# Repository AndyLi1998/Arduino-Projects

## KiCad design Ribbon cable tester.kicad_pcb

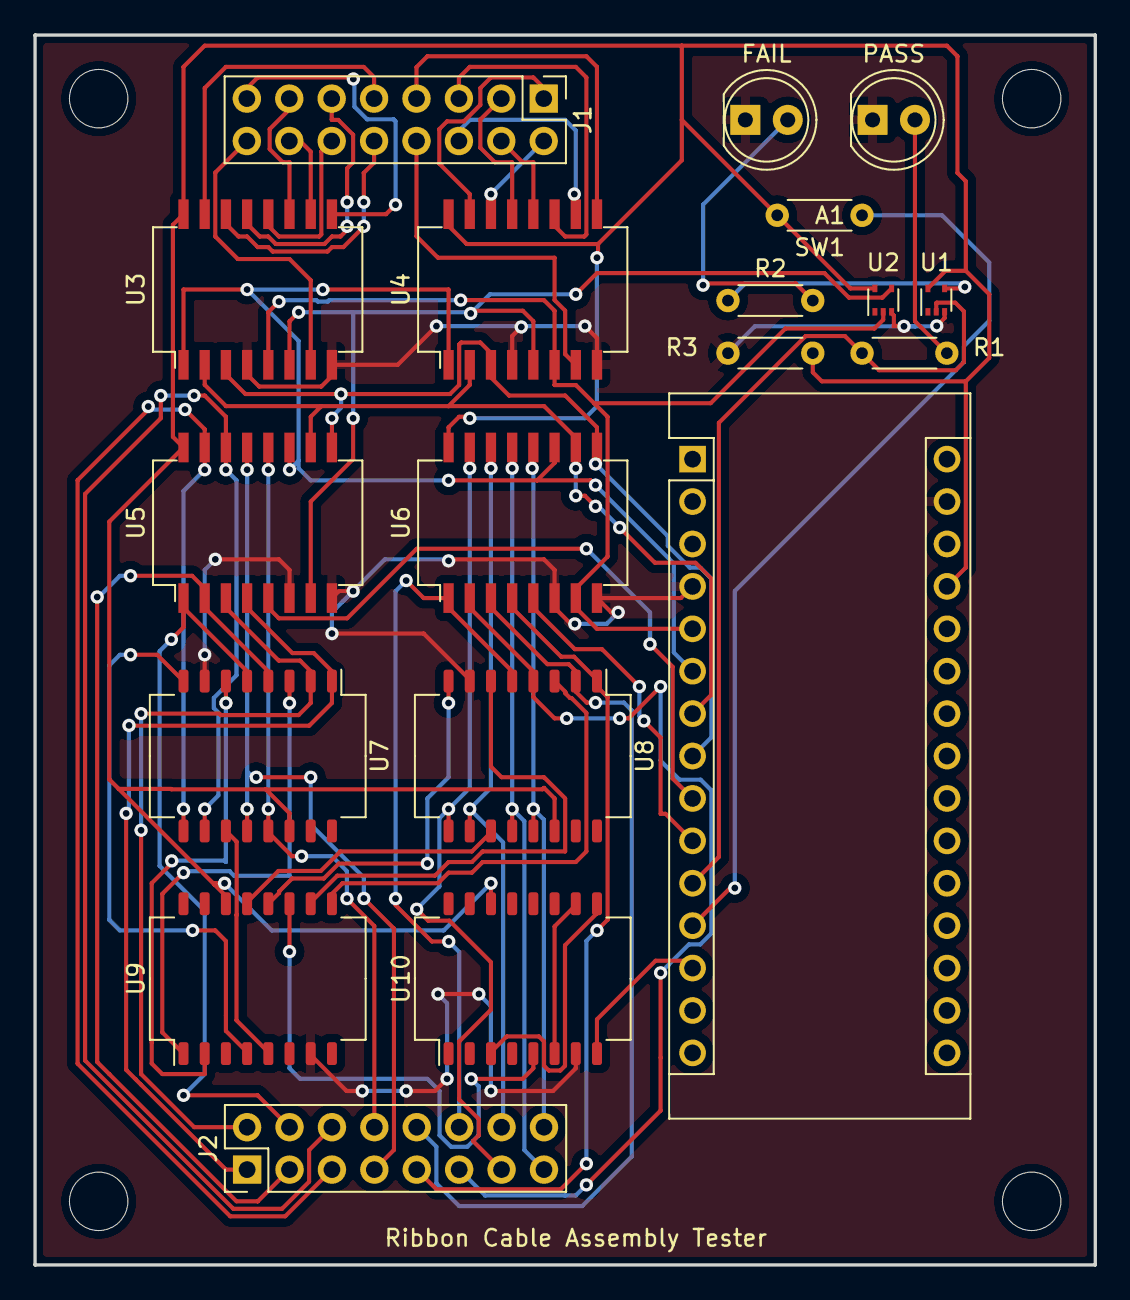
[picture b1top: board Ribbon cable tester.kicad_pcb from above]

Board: 2 copper layers, 63.5 x 73.7 mm, 19 parts (0 on the bottom side), 61 nets.

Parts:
A1: Arduino_Nano_v3.x; Arduino_Nano
FAIL: LED_Small_Filled; LED_D5.0mm
J1, J2: Conn_02x08_Counter_Clockwise; PinHeader_2x08_P2.54mm_Vertical
PASS: LED_Small_Filled; LED_D5.0mm
R1, R2, R3: R_Small_US; R_Axial_DIN0204_L3.6mm_D1.6mm_P5.08mm_Horizontal
SW1: SW_Push; R_Axial_DIN0204_L3.6mm_D1.6mm_P5.08mm_Horizontal
U1, U2: 74LVC1GU04DRL; SOT-553
U3, U4: 74HCT237; Transformer_Ethernet_Bel_S558-5999-T7-F
U5, U6: 74LS151; Transformer_Ethernet_Bel_S558-5999-T7-F
U7, U8, U9: 74LS86; Transformer_Ethernet_Halo_N2_SO-16_7.11x12.7mm
U10: 74HC86; Transformer_Ethernet_Halo_N2_SO-16_7.11x12.7mm

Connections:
/FirstRowPass: A1.9 (D6), U5.5 (Z)
/LED_Power: A1.11 (D8), R1.1, U1.2
/SecondRowPass: A1.10 (D7), U6.5 (Z)
/Sel0: A1.5 (D2), U2.2, U3.5 (~E1), U4.6 (E2), U6.7 (~E)
/Sel1: A1.6 (D3), U3.1 (A0), U4.1 (A0), U5.11 (S0), U6.11 (S0)
/Sel2: A1.7 (D4), U3.2 (A1), U4.2 (A1), U5.10 (S1), U6.10 (S1)
/Sel3: A1.8 (D5), U3.3 (A2), U4.3 (A2), U5.9 (S2), U6.9 (S2)
/Short_check: A1.13 (D10), U10.8
/Start_but: A1.12 (D9), SW1.1
/Vcc: A1.27 (+5V), R3.2, SW1.2, U1.5 (VCC), U2.5 (VCC), U3.16 (VCC), U4.16 (VCC), U5.16 (VCC), U6.16 (VCC), U7.14 (VCC), U8.14 (VCC), U9.14 (VCC), U10.14 (VCC)
/notSel0: U2.4, U3.6 (E2), U4.5 (~E1), U5.7 (~E)
/sig1: J2.1, U5.4 (I0), U7.1
/sig2: J2.2, U5.3 (I1), U7.2
/sig3: J2.3, U5.2 (I2), U7.4
/sig4: J2.4, U5.1 (I3), U7.5
/sig5: J2.5, U5.15 (I4), U7.9
/sig6: J2.6, U5.14 (I5), U7.10
/sig7: J2.7, U5.13 (I6), U7.12
/sig8: J2.8, U5.12 (I7), U7.13
/sig9: J2.9, U6.4 (I0), U8.1
/sig10: J2.10, U6.3 (I1), U8.2
/sig11: J2.11, U6.2 (I2), U8.4
/sig12: J2.12, U6.1 (I3), U8.5
/sig13: J2.13, U6.15 (I4), U8.9
/sig14: J2.14, U6.14 (I5), U8.10
/sig15: J2.15, U6.13 (I6), U8.12
/sig16: J2.16, U6.12 (I7), U8.13
GNDREF: A1.4 (GND), A1.29 (GND), FAIL.1 (K), PASS.1 (K), R3.1, U1.3 (GND), U2.3 (GND), U3.4 (~LE), U3.8 (GND), U4.4 (~LE), U4.8 (GND), U5.6 (~Z), U5.8 (GND), U6.6 (~Z), U6.8 (GND), U7.7 (GND), U8.7 (GND), U9.7 (GND), U10.7 (GND)
unnamed: PASS.2 (A), R1.2
unnamed: FAIL.2 (A), R2.2
unnamed: J1.1, U4.15 (Y0)
unnamed: J1.2, U4.14 (Y1)
unnamed: J1.3, U4.13 (Y2)
unnamed: J1.4, U4.12 (Y3)
unnamed: J1.5, U4.11 (Y4)
unnamed: J1.6, U4.10 (Y5)
unnamed: J1.7, U4.9 (Y6)
unnamed: J1.8, U4.7 (Y7)
unnamed: J1.9, U3.15 (Y0)
unnamed: J1.10, U3.14 (Y1)
unnamed: J1.11, U3.13 (Y2)
unnamed: J1.12, U3.12 (Y3)
unnamed: J1.13, U3.11 (Y4)
unnamed: J1.14, U3.10 (Y5)
unnamed: J1.15, U3.9 (Y6)
unnamed: J1.16, U3.7 (Y7)
unnamed: R2.1, U1.4
unnamed: U7.3, U9.1
unnamed: U7.6, U9.2
unnamed: U7.8, U9.4
unnamed: U7.11, U9.5
unnamed: U8.3, U9.9
unnamed: U8.6, U9.10
unnamed: U8.8, U9.12
unnamed: U8.11, U9.13
unnamed: U9.3, U10.1
unnamed: U9.6, U10.2
unnamed: U10.3, U10.9
unnamed: U9.8, U10.4
unnamed: U9.11, U10.5
unnamed: U10.6, U10.10

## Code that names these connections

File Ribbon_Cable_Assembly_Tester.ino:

int Sel0=2; 
int Sel1=3;
int Sel2=4;
int Sel3=5;
int FRP=6; //First Row Pass
int SRP=7; //Second Row Pass
int LED_Power=8; //one pin power two LED, default condition FAIL light on
int start_button=9;
int short_check=10;
int counter=0;


void setup() {
  // put your setup code here, to run once:
  pinMode(Sel0,OUTPUT);
  pinMode(Sel1,OUTPUT);
  pinMode(Sel2,OUTPUT);
  pinMode(Sel3,OUTPUT);
  pinMode(FRP,INPUT);
  pinMode(SRP,INPUT);
  pinMode(LED_Power,OUTPUT);
  pinMode(start_button,INPUT);
  pinMode(short_check,INPUT);
  Serial.begin(9600);

  
  
}

void loop() {
  // put your main code here, to run repeatedly:
  while (digitalRead(start_button)==HIGH){
    //set up inital condition: 0000
     digitalWrite(Sel0,LOW);
     digitalWrite(Sel1,LOW);
     digitalWrite(Sel2,LOW);
     digitalWrite(Sel3,LOW);

     //two rows
     for (int i=0;i<2;i++){
      // eight columns
      for (int j=0;j<8;j++){
        
        if (i==0 && digitalRead(FRP)==HIGH && digitalRead(short_check)==HIGH){ //confirming reading at first row, First Row Pass is high, 16 input XOR block output is high (only one pin is high, thus no short)
          counter=counter+1;
          if (j==0){
            // 0001
            digitalWrite(Sel3,HIGH);
          }
          else if (j==1){
            // 0010
            digitalWrite(Sel2,HIGH);
            digitalWrite(Sel3,LOW);
          }
          else if (j==2){
            //0011
            digitalWrite(Sel3,HIGH);
          }
          else if (j==3){
            //0100
            digitalWrite(Sel1,HIGH);
            digitalWrite(Sel2,LOW);
            digitalWrite(Sel3,LOW);
          }
          else if (j==4){
            //0101
            digitalWrite(Sel3,HIGH);
          }
          else if (j==5){
            //0110
            digitalWrite(Sel2,HIGH);
            digitalWrite(Sel3,LOW);
          }
          else if (j==6){
            //0111
            digitalWrite(Sel3,HIGH);
          }
          else if (j==7){
            //1000
            digitalWrite(Sel0,HIGH);
            digitalWrite(Sel1,LOW);
            digitalWrite(Sel2,LOW);
            digitalWrite(Sel3,LOW);
          }
          delay(500);
        }


        
        else if (i==1 && digitalRead(SRP)==HIGH && digitalRead(short_check)==HIGH){ //Second row, same thing
          counter=counter+1;
          if (j==0){
            // 1001
            digitalWrite(Sel3,HIGH);
          }
          else if (j==1){
            // 1010
            digitalWrite(Sel2,HIGH);
            digitalWrite(Sel3,LOW);
          }
          else if (j==2){
            //1011
            digitalWrite(Sel3,HIGH);
          }
          else if (j==3){
            //1100
            digitalWrite(Sel1,HIGH);
            digitalWrite(Sel2,LOW);
            digitalWrite(Sel3,LOW);
          }
          else if (j==4){
            //1101
            digitalWrite(Sel3,HIGH);
          }
          else if (j==5){
            //1110
            digitalWrite(Sel2,HIGH);
            digitalWrite(Sel3,LOW);
          }
          else if (j==6){
            //1111
            digitalWrite(Sel3,HIGH);
          }
          else if (j==7){
            break;
          }
          delay(500);
        }
        
      }
     }

// if all pins are continuous and no short exists, Pass light will turn on.
     if (counter==16) {
      digitalWrite(LED_Power, HIGH);
      delay(3000);
      break;
     }
     else {
      digitalWrite(LED_Power, LOW);
      delay(3000);
      break;
     }

    
  }
}

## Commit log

2022-03-12 Add files via upload
    Automated hydroponic system sensor testing
2022-03-28 Ribbon test KiCAD PCB files
